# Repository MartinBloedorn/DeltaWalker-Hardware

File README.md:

# DeltaWalker-Hardware
PCB and STL files for the DeltaWalker robot. 

The DeltaWalker is a first attempt at building a quadruped walker with legs in delta configuration. 

For more info, please check the [Hackaday Project](https://hackaday.io/project/66121-deltawalker).

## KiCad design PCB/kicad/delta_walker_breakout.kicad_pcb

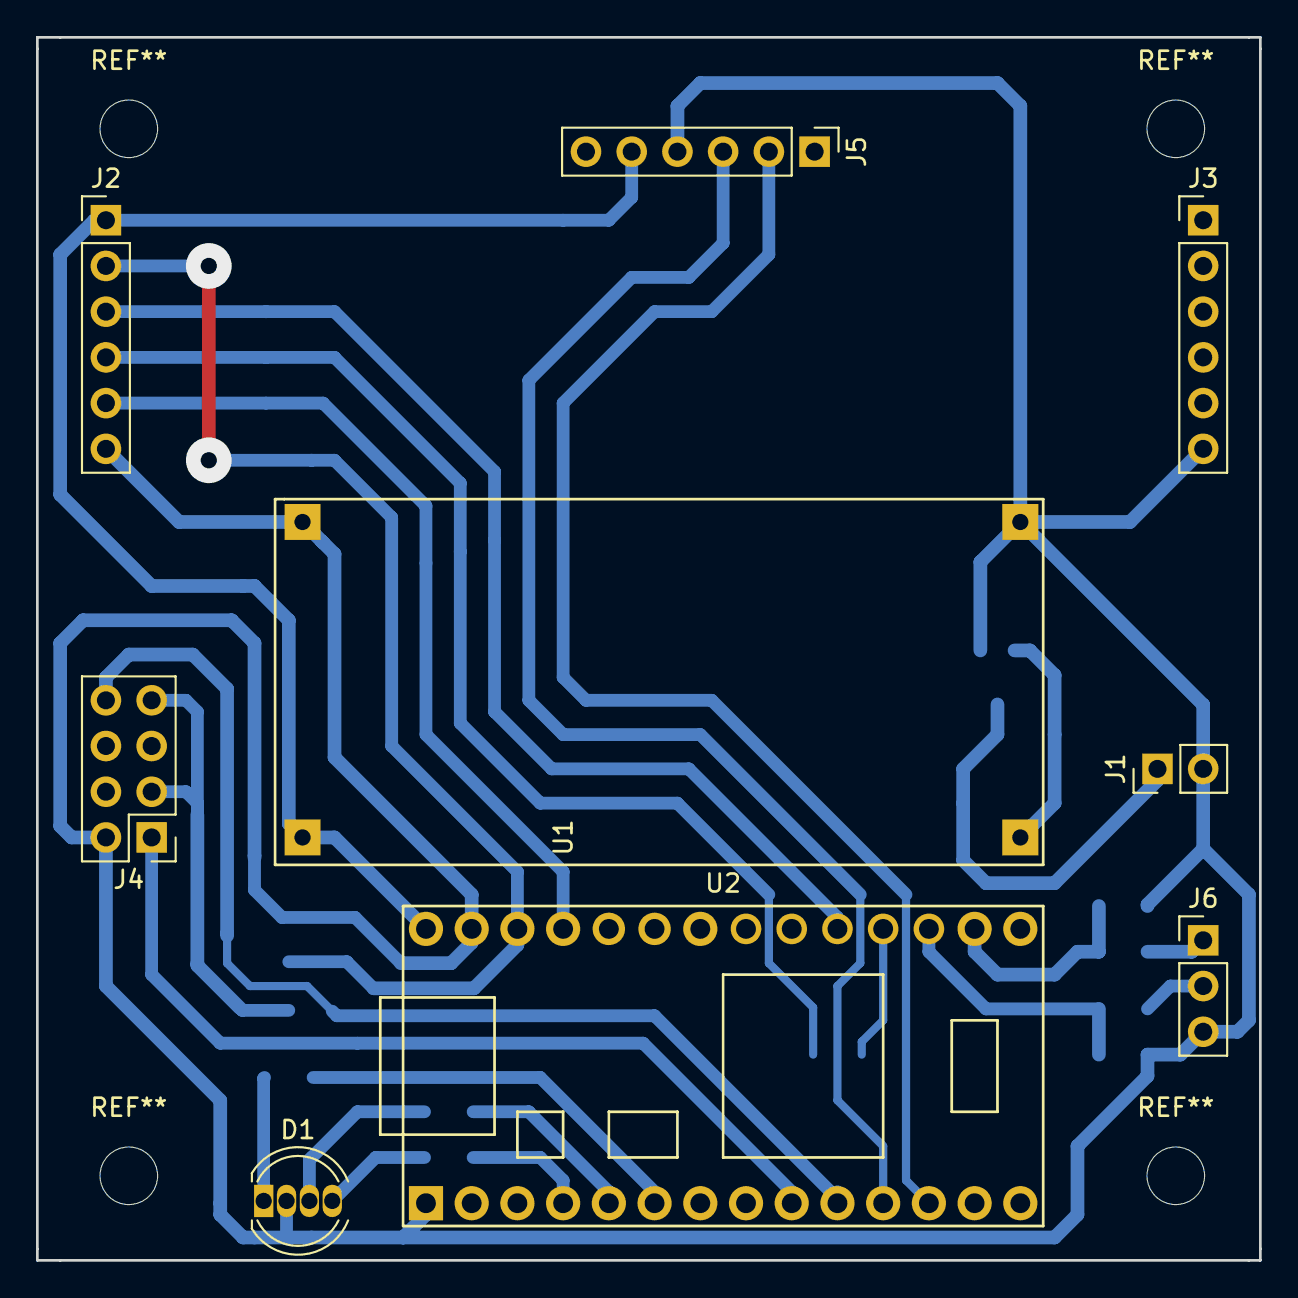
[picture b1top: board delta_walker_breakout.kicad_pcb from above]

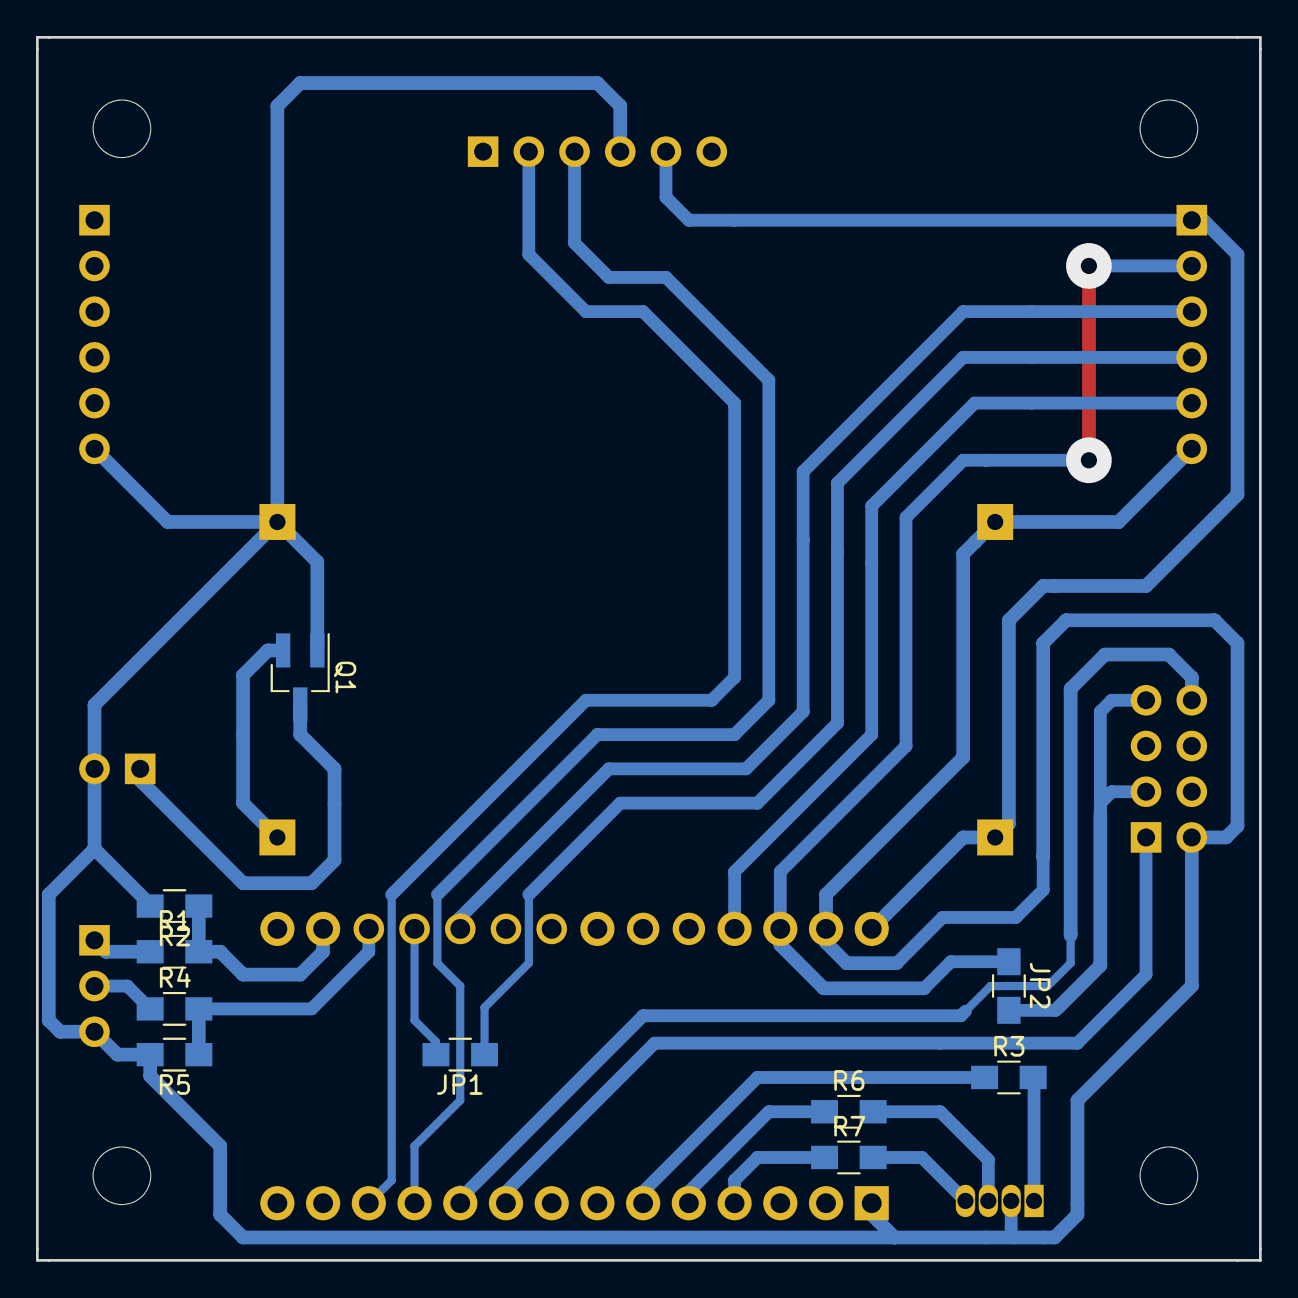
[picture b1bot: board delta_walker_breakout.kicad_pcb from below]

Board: 2 copper layers, 67.9 x 67.9 mm, 19 parts (10 on the bottom side), 24 nets.

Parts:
D1: LED_RCGB; LED_D5.0mm-4
J1: Conn_01x02; Pin_Header_Straight_1x02_Pitch2.54mm
J2, J3, J5: Conn_01x06; Pin_Header_Straight_1x06_Pitch2.54mm
J4: Conn_02x04_Odd_Even; Pin_Header_Straight_2x04_Pitch2.54mm
J6: Conn_01x03; Pin_Header_Straight_1x03_Pitch2.54mm
JP1, JP2: Jumper_NO_Small; R_0805_HandSoldering
Q1: Q_PMOS_GSD; SOT-23_Handsoldering
R1, R2, R3, R4, R5, R6, R7: R; R_0805_HandSoldering
U1: LM2596-MOD
U2: Teensy3.1; Teensy30_31_32_LC_min

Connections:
+3V3: J2.2, JP2.1, U2.31
+5V: J2.1, J3.1, J5.5, U1.3, U2.33
/BT_RX: J5.2, U2.12
/BT_TX: J5.3, U2.11
/ESP_RX: J4.8, U2.10
/ESP_TX: J4.1, U2.9
/LED_0: R3.1, U2.6
/LED_1: R6.1, U2.5
/LED_2: R7.1, U2.4
/LIPO_CELL_0_V: R1.2, R2.1, U2.21
/LIPO_CELL_1_V: R4.2, R5.1, U2.22
/OE: J2.5, U2.30
/SCL: J2.4, JP1.1
/SDA: J2.3, U2.24
GND: D1.2, J1.2, J2.6, J3.6, J4.2, J5.4, J6.3, Q1.1, R2.2, R5.2, U1.2, U1.4, U2.1, U2.32
unnamed: D1.1, R3.2
unnamed: D1.3, R6.2
unnamed: D1.4, R7.2
unnamed: J1.1, Q1.3
unnamed: J4.3, J4.7, JP2.2
unnamed: J6.1, R1.1
unnamed: J6.2, R4.1
unnamed: JP1.2, U2.23
unnamed: Q1.2, U1.1

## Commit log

2018-02-25 Adding DeltaWalker PCB and STL files; adding RemoteControl STL files as well.
